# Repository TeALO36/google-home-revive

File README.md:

# Google Home Revive

Deux cartes électroniques de remplacement pour le **Google Home de 1re génération (2016)**, pour le transformer en
assistant vocal local et ouvert sous **Home Assistant** (ESPHome). Le boîtier, le haut-parleur et l'anneau lumineux
d'origine sont conservés ; l'électronique Google est remplacée.

- Carte mère : même forme et mêmes trous de fixation que l'originale, USB-C, ampli classe D, coupure micro matérielle.
- Carte du dessus : 2 micros numériques, anneau de 12 LED RGB, anneau tactile capacitif et touche centrale.
- Liaison entre les deux cartes : 10 fils soudés (des câbles Dupont coupés suffisent).
- **Les pièces délicates sont soudées en usine par JLCPCB** (micros, contrôleur tactile, ampli, USB-C, tous les petits
  passifs). Il reste à souder au fer des pièces à pattes visibles, listées plus bas avec leur emplacement.

## Aperçu des cartes

| | Face composants | Face arrière |
|---|---|---|
| Carte mère (107,6 x 49 mm, 2 couches) |  |  |
| Carte du dessus (diamètre 74,8 mm, 2 couches) |  |  |

Les deux cartes passent le contrôle DRC de KiCad sans erreur ni connexion manquante (rapports :
`hardware/*/gh_*_drc.json`).

## Fonctions

| Fonction | Réalisation |
|---|---|
| Processeur principal | ESP32-S3-WROOM-1-N16R8 (Wi-Fi, 16 Mo de flash, 8 Mo de PSRAM) |
| Mot d'activation | « Hey Jarvis » détecté sur l'appareil (micro_wake_word), pipeline vocal Home Assistant |
| Micros | 2 x Infineon IM69D130 (SNR 69 dB(A), AOP 130 dB SPL), meilleurs que les InvenSense INMP621 d'origine (65 dB(A)) |
| Annulation d'écho | référence I2S renvoyée par l'ampli (SDOUT du TAS5805M) vers l'S3 |
| Ampli | TI TAS5805M (I2S, DSP intégré, pont BTL) |
| Bluetooth | ESP32-WROOM-32E dédié en récepteur A2DP, flashé à travers l'S3 |
| Tactile | MPR121 : anneau de 10 secteurs (rotation horaire = volume +, antihoraire = volume -) et touche ronde au centre ; appui bref n'importe où = pause / lecture, double appui = piste suivante |
| LED | 12 LED RGB adressables WS2812B-MINI-V3J (couleur 24 bits réglable LED par LED) sous le diffuseur d'origine : animations arc-en-ciel, comète, scintillement, etc., pilotables depuis Home Assistant |
| Coupure micro | interrupteur matériel : l'horloge des micros est coupée physiquement, l'état est lu par l'S3 |
| Alimentation / service | USB-C vertical (flash, journaux) |
| Configuration Wi-Fi | point d'accès + page de configuration, l'adresse IP est annoncée à voix haute |

Cahier des charges complet : [docs/cahier_des_charges.md](docs/cahier_des_charges.md).

## Coût

Prix relevés le 14/11/2026 (devis JLCPCB, stock JLC et LCSC), taux 1 $ = 0,86 EUR, livraison en France, TVA 20 % et
taxe petits colis comprises. Une seule commande JLCPCB + LCSC, sous le seuil de 150 EUR (pas de frais de dédouanement).

| Commande | USD TTC | EUR TTC |
|---|---:|---:|
| **1 appareil** (+ 1 jeu de cartes pré-assemblées en réserve) | **129,13** | **111,06** |
| **2 appareils** dans la même commande | **142,27** | **122,35** |
| **Coût moyen par appareil, commande de 2** | **71,13** | **61,17** |

JLCPCB assemble au minimum **2 exemplaires** de chaque carte et fabrique au minimum **5 PCB**. Le 2e jeu assemblé coûte
environ 20 $ (20 EUR TTC) de plus que le 1er ; les 3 PCB nus restants sont compris dans le prix minimum de 5. Le plus
rentable est donc d'en faire deux (ou de partager la commande). Avec l'application de bureau JLCPCB, les PCB sont
4 $ moins chers : 106,93 EUR pour 1 appareil, 59,11 EUR par appareil pour 2.

Détail ligne par ligne : [docs/devis_partiel.md](docs/devis_partiel.md). Autres scénarios : tout assemblé par JLCPCB
(~129 EUR par appareil, [docs/devis_assemble.md](docs/devis_assemble.md)), ou kit entièrement soudé à l'air chaud
(~71 EUR, [docs/devis.md](docs/devis.md)).

## Commander

Chaque carte a trois fichiers dans `hardware/<carte>/fab/` :

| Fichier | Où l'envoyer | Contenu |
|---|---|---|
| `gh_<carte>_gerbers.zip` | JLCPCB | le circuit imprimé |
| `gh_<carte>_bom.csv` + `gh_<carte>_cpl.csv` | JLCPCB (assemblage) | pièces soudées en usine et leur position |
| `gh_<carte>_hand_bom.csv` | LCSC (pas JLCPCB) | pièces à souder soi-même |

### 1. JLCPCB : PCB + assemblage des pièces délicates

À faire deux fois, d'abord pour `mainboard`, puis pour `topboard` :

1. Sur jlcpcb.com, « Order now », puis « Add gerber file » : choisir `gh_<carte>_gerbers.zip`.
2. Options du PCB : 2 couches, épaisseur 1,6 mm, finition **HASL sans plomb** (« LeadFree HASL », exigée pour
   l'assemblage), vias « Tented », quantité 5.
3. En bas de la page, activer **« PCB Assembly »** :
   - type **Economic** ;
   - face assemblée **Top** ;
   - quantité assemblée **2** (minimum imposé) ;
   - valider.
4. Page suivante : « Add BOM File » = `gh_<carte>_bom.csv`, « Add CPL File » = `gh_<carte>_cpl.csv`, puis
   « Process BOM & CPL ».
5. Liste des pièces : toutes doivent être trouvées et cochées. Si une pièce est en rupture, choisir un équivalent de
   même valeur et même boîtier. Ne pas téléverser `gh_<carte>_hand_bom.csv` ici.
6. Vérification des placements : la vue montre chaque pièce sur la carte. Contrôler l'orientation du TAS5805M (U3),
   du transistor Q1 et de l'USB-C (J1) pour la carte mère, des micros (MK1, MK2) et du MPR121 (U1) pour la carte du
   dessus : les pattes doivent tomber sur les pastilles et le point rose (broche 1) sur le repère triangulaire de la
   sérigraphie. Une pièce tournée ou décalée se corrige dans cette vue : la sélectionner, puis boutons de rotation ou
   flèches du clavier. Les ingénieurs JLCPCB revérifient aussi les placements avant la production.
   Seules les pièces de `gh_<carte>_bom.csv` apparaissent : les modules ESP32, bobines, C1, etc. sont absents, c'est
   normal (à souder soi-même).
7. « Save to cart ».

Les deux cartes se paient ensemble dans le panier. Appliquer le coupon SMT mensuel (9 $) s'il est proposé.

### 2. LCSC : pièces à souder soi-même

1. Sur lcsc.com, ouvrir l'outil « BOM Tool » et téléverser `hardware/mainboard/fab/gh_mainboard_hand_bom.csv`, puis
   `hardware/topboard/fab/gh_topboard_hand_bom.csv` (colonne « LCSC Part # »).
2. Pour 2 appareils, doubler les quantités. LCSC impose parfois un minimum (5 ou 10 pièces pour les petits circuits) :
   accepter, le surplus coûte quelques centimes.
3. Au paiement, regrouper l'envoi avec la commande JLCPCB (option de colis combiné) pour payer une seule livraison.
4. Ajouter un paquet de **câbles Dupont femelle-femelle de 20 cm** (n'importe quel vendeur) si vous n'en avez pas.

Avant de commander, vérifier la mécanique (section 8 du cahier des charges) sur l'appareil réel.

## Ce qu'il faut souder soi-même

<p align="center">
  
</p>

Le [manuel de soudure](docs/manuel_soudure.md) reprend tout pas à pas : liste des composants face par face, plans,
technique pour chaque type de pièce, fils de liaison et contrôles avant la mise sous tension. Résumé ci-dessous.

Les cartes arrivent avec les pièces délicates déjà soudées. Restent uniquement des pièces dont les pattes sont visibles
et accessibles à la panne du fer. Sur les plans, **en orange : à souder soi-même**, en gris : déjà soudé par JLCPCB.

Outillage : fer à panne fine (biseau 1 à 2 mm), étain 0,5 mm, flux, tresse à dessouder, pince brucelles, loupe.
Pas d'air chaud nécessaire. Ordre conseillé : petits circuits d'abord, puis bobines, condensateur, modules, connecteur.

### Carte mère (face composants)

| Repère | Pièce | Lien LCSC | Qté | Boîtier | Variantes et pièges |
|---|---|---|---:|---|---|
| U1 | ESP32-S3-WROOM-1-N16R8 | [C2913202](https://www.lcsc.com/product-detail/C2913202.html) | 1 | module 18 x 25,5 mm, pattes crénelées | N8R8 ou N16R2 conviennent (PSRAM obligatoire). Éviter WROOM-1U (antenne externe), WROOM-2 et MINI (brochage différent). |
| U2 | ESP32-WROOM-32E-N4 | [C701341](https://www.lcsc.com/product-detail/C701341.html) | 1 | module 18 x 25,5 mm | N8 / N16 conviennent. Éviter WROOM-32UE (antenne externe) et WROVER. |
| U4 | TPS54302DDCR | [C311983](https://www.lcsc.com/product-detail/C311983.html) | 1 | SOT-23-6 (« DDC ») | Régulateur 5 V. Pas de TPS54202 (autre brochage). |
| U5 | TLV62569DBVR | [C141836](https://www.lcsc.com/product-detail/C141836.html) | 1 | SOT-23-5 (« DBV ») | Régulateur 3,3 V. Pas la version DRL (boîtier SOT-563, plus petit). |
| U6 | USBLC6-2SC6 | [C7519](https://www.lcsc.com/product-detail/C7519.html) | 1 | SOT-23-6 | Protection USB. Repère du point = broche 1. |
| U7 | 74LVC1G74DP | [C548409](https://www.lcsc.com/product-detail/C548409.html) | 1 | TSSOP-8 3 x 3 mm (« DP ») | Bascule du mute. Pas les suffixes DC ou GT (boîtiers plus petits). |
| U8 | SN74LVC1G14DBVR | [C7835](https://www.lcsc.com/product-detail/C7835.html) | 1 | SOT-23-5 (« DBV ») | Pas la version DCK (SC-70, plus petite). |
| U9 | SN74LVC1G125DBVR | [C23654](https://www.lcsc.com/product-detail/C23654.html) | 1 | SOT-23-5 (« DBV ») | Pas la version DCK. |
| L1 | 10 uH | [C602032](https://www.lcsc.com/product-detail/C602032.html) | 1 | bobine blindée 4 x 4 mm | Toute bobine blindée 4 x 4 mm de même valeur et de courant au moins égal. |
| L2 | 2,2 uH | [C602029](https://www.lcsc.com/product-detail/C602029.html) | 1 | bobine blindée 4 x 4 mm | idem |
| L3, L4 | 4,7 uH | [C602031](https://www.lcsc.com/product-detail/C602031.html) | 2 | bobine blindée 4 x 4 mm | idem (filtre de sortie de l'ampli) |
| C1 | 220 uF / 25 V | [C696188](https://www.lcsc.com/product-detail/C696188.html) | 1 | électrolytique CMS 6,3 x 6,6 mm | **Polarisé** : la bande noire (moins) va du côté du coin non biseauté de l'empreinte. 25 V minimum. |
| J3 | JST ZH 2 broches, CMS horizontal | [C265329](https://www.lcsc.com/product-detail/C265329.html) | 1 | S2B-ZR-SM4A-TF | Connecteur du haut-parleur. Réutiliser la fiche d'origine si elle est au pas de 1,5 mm, sinon souder les fils sur les pastilles. |

### Carte mère (face arrière)

Une seule pièce : le **jack d'alimentation d'origine** (J2), à dessouder de la carte Google et à ressouder au même
endroit (empreinte copiée de l'originale, 2 ergots de centrage). Il n'est pas commandé : on réutilise le sien.

Les deux modules ESP32 se soudent comme de gros composants : étamer une pastille d'angle, poser le module, chauffer
l'angle, vérifier l'alignement, puis souder les autres pattes. Le plan de masse sous le module n'a pas besoin d'être
soudé.

### Carte du dessus

Face arrière (vue carte retournée) : les 12 LED, tournées vers le diffuseur.

Face composants : le tampon de niveau des LED.

| Repère | Pièce | Lien LCSC | Qté | Boîtier | Variantes et pièges |
|---|---|---|---:|---|---|
| D1 à D12 | WS2812B-MINI-V3J | [C22371519](https://www.lcsc.com/product-detail/C22371519.html) | 12 | 3,5 x 3,5 mm, 4 pattes en J | Uniquement cette version « MINI-V3J » : les WS2812B-2020 ou 1515 n'ont pas de pattes accessibles au fer, la WS2812B 5050 est trop grande. Orientation : broche 1 = VDD (+5 V), suivre le plan KiCad (`hardware/topboard/gh_topboard.kicad_pcb`). |
| U2 | SN74AHCT1G125DBVR | [C7484](https://www.lcsc.com/product-detail/C7484.html) | 1 | SOT-23-5 (« DBV ») | **AHCT** obligatoire (entrée compatible 3,3 V, sortie 5 V) : pas de version AHC ni LVC. |

Les photos et la documentation de chaque pièce sont sur sa page LCSC (lien ci-dessus) : comparer le boîtier et le
marquage avant de commander une variante.

### Liaison entre les cartes : 10 fils

Pastilles J4 (carte mère) et J1 (carte du dessus), au pas de 2,54 mm, dans cet ordre :

| Broche | Signal | Broche | Signal |
|---|---|---|---|
| 1 | +5 V | 6 | SCL |
| 2 | GND | 7 | VMIC |
| 3 | données LED | 8 | DAT (micros) |
| 4 | +3,3 V | 9 | GND |
| 5 | SDA | 10 | CLK (micros) |

1. Prendre une nappe de 10 câbles Dupont femelle-femelle de 20 cm (ils restent collés côte à côte).
2. Couper les connecteurs aux deux bouts, garder une longueur de **12 à 15 cm**.
3. Dénuder 2 mm, torsader les brins, étamer.
4. Étamer les pastilles, poser chaque fil à plat sur sa pastille et chauffer. Même ordre des deux côtés.
5. **Torsader ensemble les fils 9 (GND) et 10 (CLK)** sur toute la longueur.
6. Vérifier au multimètre qu'il n'y a pas de court-circuit entre +5 V, +3,3 V et GND avant la première mise sous tension.

Variante démontable : souder une barrette de 10 broches mâles CMS au pas de 2,54 mm sur J4 de la carte mère et
garder les connecteurs Dupont de ce côté.

## Firmware

### Premier flash (ESP32-S3, ESPHome)

```bash
pip install esphome
cd firmware/s3
cp secrets.example.yaml secrets.yaml      # Wi-Fi (facultatif), mots de passe et clé API
esphome run gh-revive.yaml                # brancher l'USB-C ; ensuite les mises à jour passent par OTA
```

Si l'S3 n'est pas détecté, maintenir la pastille TP2 (BOOT) à la masse en branchant l'USB-C.

### Configuration du Wi-Fi

- **Identifiants au flash** : renseigner `wifi_ssid` / `wifi_password` dans `secrets.yaml`, l'appareil s'y connecte
  directement.
- **Sans identifiants** (ou réseau injoignable pendant 30 s) : l'appareil ouvre le point d'accès **« GH-Revive
  Setup »** (mot de passe : `ap_password` de `secrets.yaml`) et le haut-parleur le dit toutes les minutes. En s'y
  connectant, le téléphone ouvre la page de configuration :
  1. **mot de passe administrateur** : créé à la première visite (8 caractères minimum, saisi deux fois), demandé
     ensuite pour toute modification ;
  2. **réseau Wi-Fi** : choisi dans la liste des réseaux détectés ou saisi à la main, puis la clé ;
  3. la connexion est **testée en direct** : « clé incorrecte », « réseau introuvable » ou « sécurité non prise en
     charge » s'affichent, et l'on corrige pour réessayer.
- Une fois connecté, le haut-parleur **annonce l'adresse IP** (« Connecté au Wi-Fi. Mon adresse est : 1 9 2 point
  1 6 8 ... »). Le bouton « Annoncer l'adresse IP » dans Home Assistant la répète.
- La même page reste accessible sur le réseau local à `http://<adresse IP>/`, protégée par le mot de passe
  administrateur.
- **WEP** : non pris en charge. La pile Wi-Fi de l'ESP32 ne gère que WPA, WPA2 et WPA3 ; le WEP est cassable en
  quelques minutes et absent des box récentes. Passer la box en WPA2.

### Plusieurs appareils dans la maison

Aucune intégration Home Assistant spécifique n'est nécessaire : chaque appareil est un appareil ESPHome standard,
découvert automatiquement par l'intégration ESPHome de Home Assistant.

- **Même firmware pour tous** : le nom reçoit automatiquement la fin de l'adresse MAC (`gh-revive-a1b2c3`), donc
  plusieurs appareils cohabitent sans conflit. On les renomme ensuite dans Home Assistant (« Salon », « Chambre »).
- **Une pièce par appareil** : assigner chaque appareil à sa pièce (« Zone » dans Home Assistant). « Jarvis, allume la
  lumière » allume alors la lumière de la pièce où se trouve l'appareil qui a répondu.
- **Où se règle le mot d'activation** : réglage « Detection du mot d'activation » de chaque enceinte.
  - « Sur l'appareil » (par défaut) : l'enceinte reconnaît elle-même « Hey Jarvis », « Okay Nabu » ou « Hey Mycroft » ;
    le mot se choisit dans Home Assistant, page de l'appareil (« Mot d'activation »). Le micro ne part vers le serveur
    qu'après le mot d'activation, et l'arbitrage de proximité ci-dessous fonctionne.
  - « Dans Home Assistant » : c'est le moteur de mot d'activation du pipeline Assist qui décide (module openWakeWord à
    installer, puis Paramètres > Assistants vocaux > Assist > mot d'activation). Le mot réglé dans Assist vaut pour
    toutes les enceintes réglées ainsi, y compris un modèle personnalisé. En contrepartie, chaque enceinte envoie le
    son du micro au serveur en continu, et l'arbitrage de proximité ne s'applique pas (Home Assistant garde la
    première enceinte qui l'a entendu).
  - Le téléphone se règle à part, dans l'application.
- **L'enceinte la plus proche répond** : quand plusieurs enceintes entendent le mot d'activation, chacune envoie aux
  autres (UDP, port 18511, réseau local) le volume auquel elle l'a entendu, attend le « Delai d'arbitrage » (400 ms
  par défaut), et seule la plus forte démarre l'écoute. Dans une pièce ouverte avec mezzanine, l'enceinte de la
  chambre répond quand on parle depuis le lit. « Niveau dernier mot d'activation » (diagnostic) montre le volume
  mesuré ; « Correction niveau micro » (±15 dB) compense une enceinte posée dans un coin ou derrière un objet.
- **Le téléphone en main est prioritaire** : le téléphone ne participe pas à l'arbitrage, mais il envoie le son à Home
  Assistant dès qu'il entend le mot d'activation, pendant que les enceintes attendent encore. Home Assistant garde le
  premier arrivé : si le téléphone a entendu, c'est lui qui répond et affiche le texte compris. Si le téléphone gagne
  trop rarement, augmenter le « Delai d'arbitrage » (jusqu'à 1,5 s, réponse un peu plus lente).
- **Pas de double exécution** : Home Assistant refuse tout second démarrage pour le même mot d'activation
  (`duplicate_wake_up_detected`), ce qui couvre aussi une annonce UDP perdue. Une commande n'est exécutée qu'une fois.
  Sur les appareils écartés, l'anneau reste éteint, sans signal d'erreur.
- **Texte compris et réponse** : « Derniere demande » et « Derniere reponse » affichent dans l'application Home
  Assistant ce que l'enceinte a compris et répondu (page de l'appareil ou carte de tableau de bord).
- **Sensibilité** : « Sensibilite mot d'activation » (Faible / Normale / Forte) règle chaque appareil, pour tous les
  modèles.
- Configurer les appareils un par un : tant qu'ils ne sont pas connectés, ils ouvrent tous le même point d'accès
  « GH-Revive Setup ».

### Module Bluetooth (PlatformIO)

Le module Bluetooth n'a pas de port USB : l'S3 sert de pont USB-C vers le module le temps de le programmer.

```bash
cd firmware/bt
pio run -e bridge -t upload --upload-port COMx    # l'S3 devient un pont USB <-> UART vers le module
pio run -e bt -t upload --upload-port COMy        # programme le module (nouveau port COM du pont)
esphome run ../s3/gh-revive.yaml                  # remet le firmware principal sur l'S3
```

### Tests unitaires (sur PC)

```bash
g++ -std=c++17 -Wall -Wextra -Werror -I firmware/s3 firmware/tests/test_ring_gesture.cpp -o test_ring && ./test_ring
g++ -std=c++17 -Wall -Wextra -Werror -I firmware/s3 firmware/tests/test_ip_speech.cpp -o test_ip && ./test_ip
g++ -std=c++17 -Wall -Wextra -Werror -I firmware/s3 firmware/tests/test_wake_arbiter.cpp -o test_arbiter && ./test_arbiter
```

### État du firmware

Fonctionnel dans la configuration : Wi-Fi avec portail de configuration et annonce vocale de l'IP, OTA, mot
d'activation et assistant vocal, lecteur multimédia avec atténuation pendant la voix, démarrage de l'ampli, anneau
tactile, LED, mute, pilotage du module Bluetooth. Reste à développer : l'annulation d'écho avec ESP-SR (composant ESP-IDF
dédié) et le relais du flux Bluetooth vers l'ampli (l'S3 n'a que deux périphériques I2S, voir la section 10 du cahier
des charges).

Messages vocaux : voix Piper `fr_FR-siwis-medium` (corpus SIWIS, licence CC BY 4.0), voir
[firmware/s3/sounds/README.md](firmware/s3/sounds/README.md).

## Contenu du dépôt

```
hardware/
  mainboard/            carte mère : projet KiCad 10, aperçus, rapport DRC
    fab/                gerbers.zip, bom.csv + cpl.csv (JLCPCB), hand_bom.csv (LCSC)
  topboard/             carte du dessus : idem
  lib/gh_revive.pretty  empreintes spécifiques (micros, LED, électrodes, pastilles de liaison)
firmware/
  s3/                   ESPHome pour l'ESP32-S3 (voix, média, tactile, LED, ampli, mute, Wi-Fi)
    components/gh_setup portail de configuration Wi-Fi (mot de passe admin, test de clé)
    sounds/             messages vocaux FLAC et leur générateur
  bt/                   PlatformIO : récepteur Bluetooth A2DP + pont de flashage USB
  homeassistant/        automatisation des gestes (double tap = piste suivante)
  tests/                tests unitaires (gestes, annonce de l'IP)
docs/                   cahier des charges, devis, plans de soudure (img/)
tools/                  génération des cartes (KiCad Python + FreeRouting) et calcul des devis
```

## Régénérer les cartes

Les cartes sont décrites en Python (`tools/ghrevive/`) et générées avec KiCad 10 et FreeRouting :

```bash
"C:/Program Files/KiCad/10.0/bin/python.exe" tools/build.py all              # placement, routage, DRC, fichiers JLC, plans
"C:/Program Files/KiCad/10.0/bin/python.exe" tools/quote_partial.py          # devis retenu
"C:/Program Files/KiCad/10.0/bin/python.exe" tools/quote_assembled.py        # devis tout assemblé
"C:/Program Files/KiCad/10.0/bin/python.exe" tools/quote.py                  # devis kit
```

La répartition usine / soudure manuelle se règle dans `HAND_REFS` (`tools/ghrevive/mainboard.py`) et le champ
`hand=True` des pièces (`tools/ghrevive/topboard.py`).

## Licence

MIT, voir [LICENSE](LICENSE). Projet indépendant, sans lien avec Google. « Google Home » est une marque de Google LLC.
Messages vocaux sous CC BY 4.0 (voir ci-dessus).

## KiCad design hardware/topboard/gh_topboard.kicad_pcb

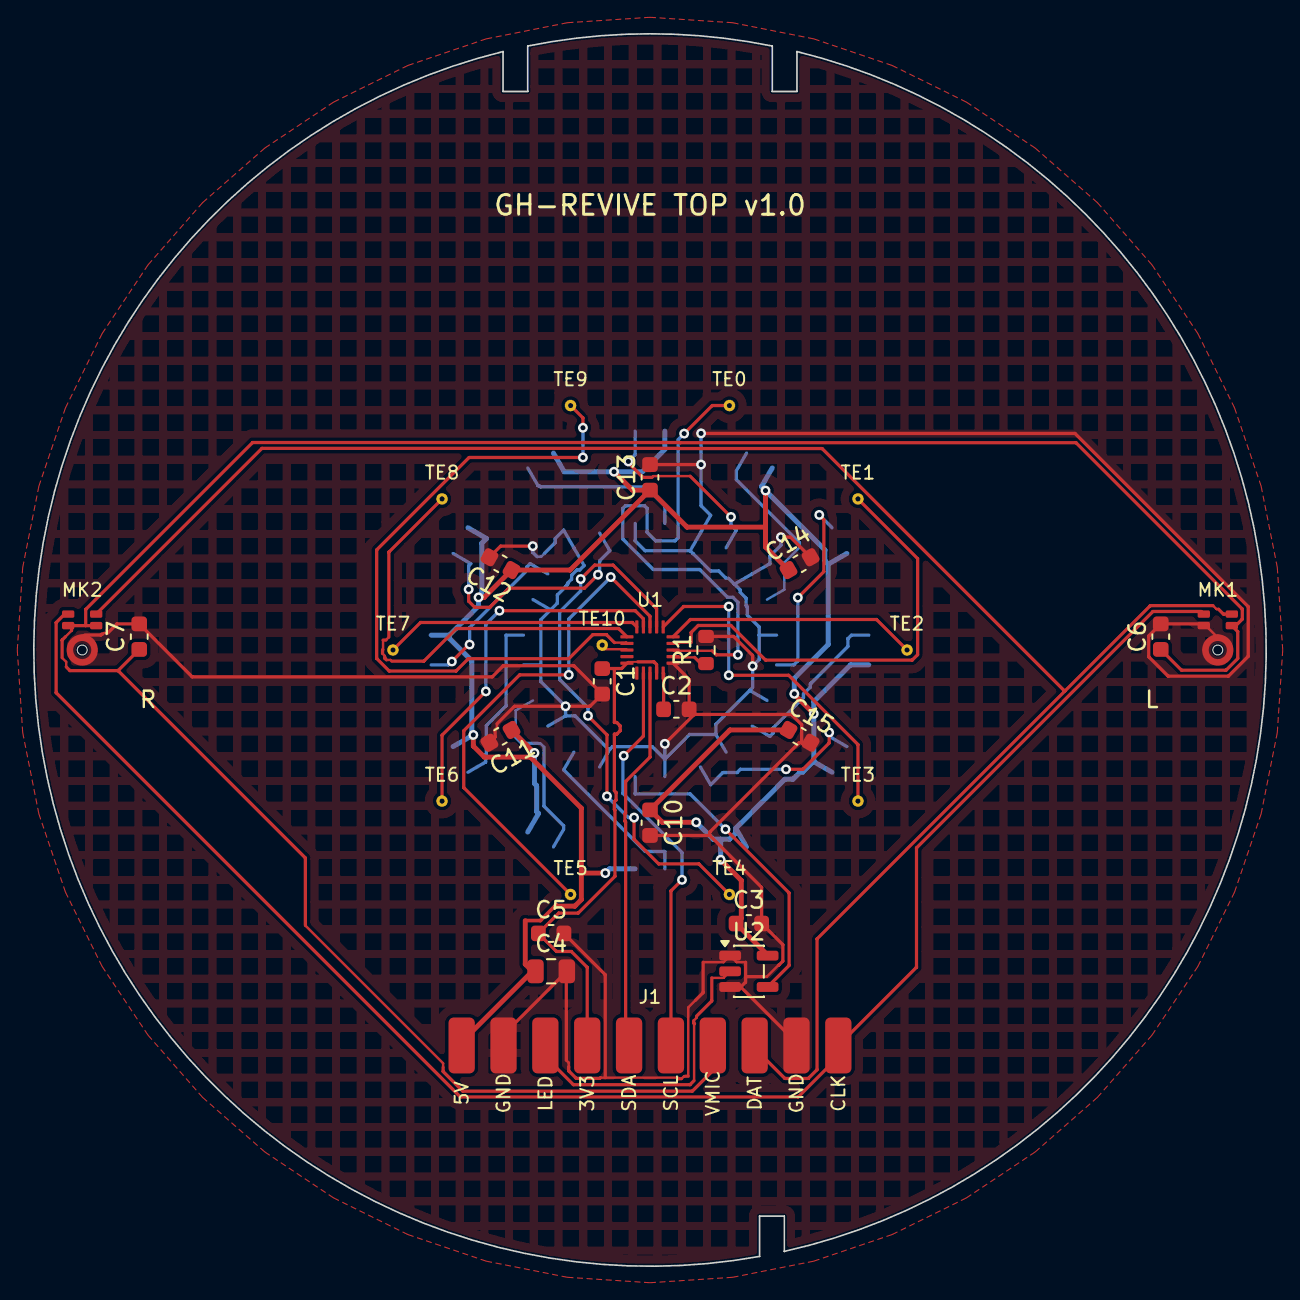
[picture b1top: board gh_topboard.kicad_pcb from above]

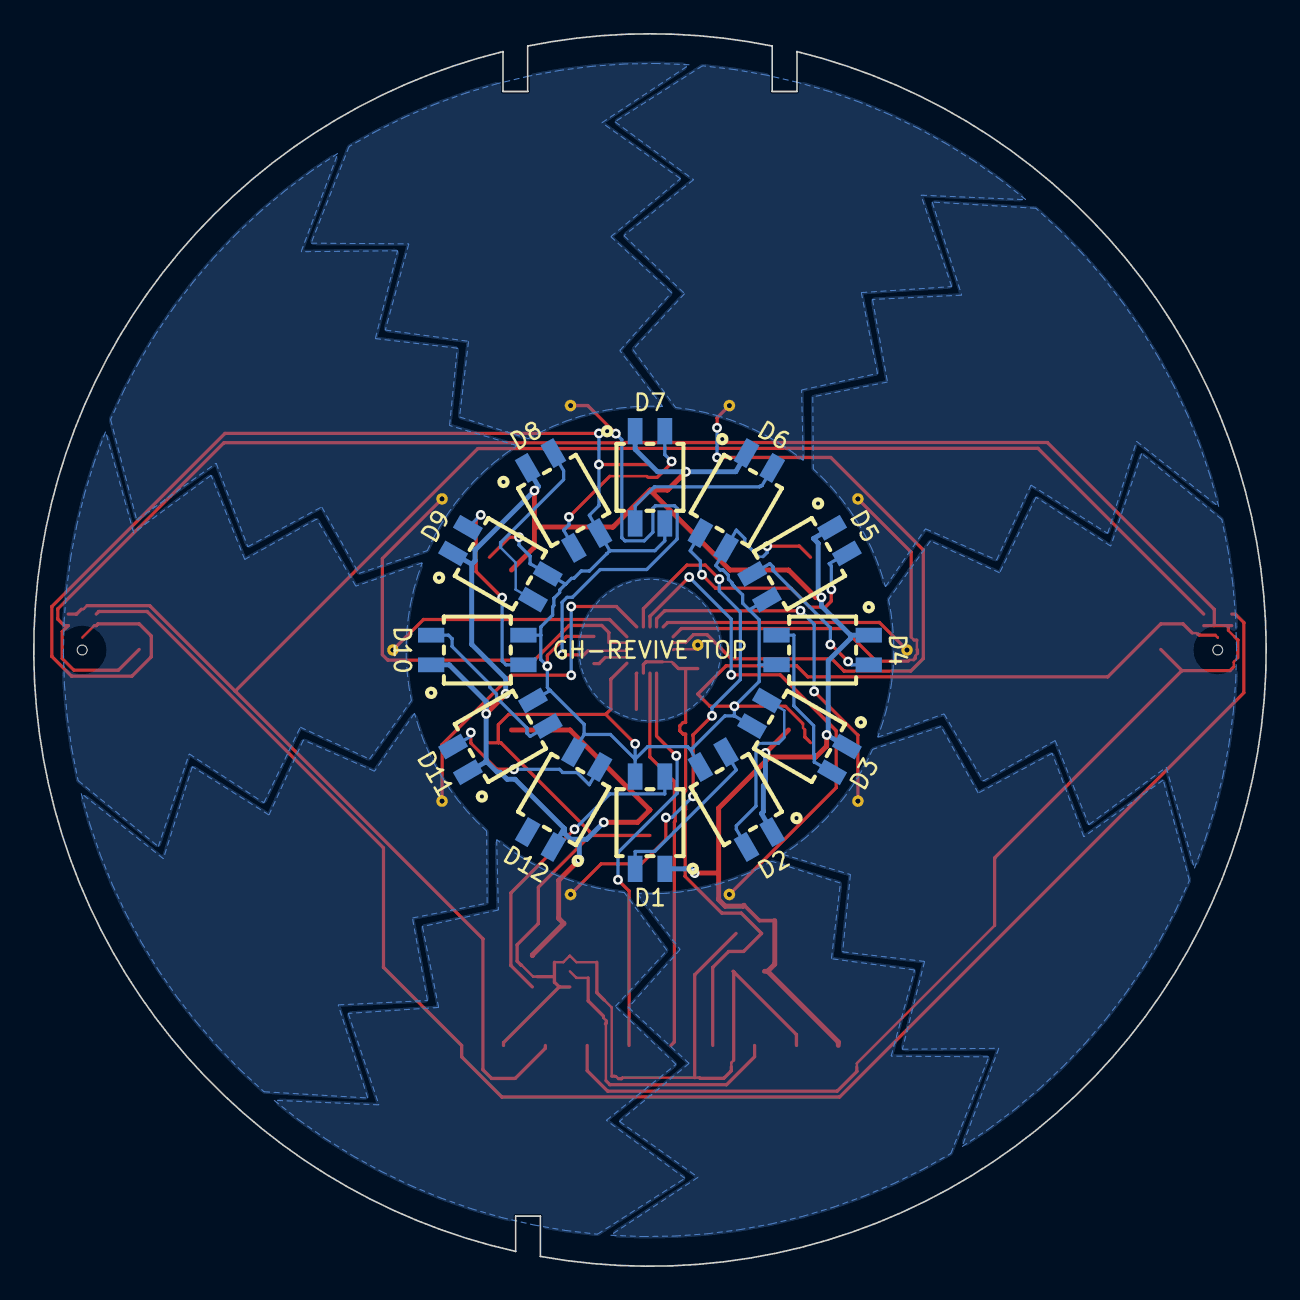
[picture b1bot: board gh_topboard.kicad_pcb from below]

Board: 2 copper layers, 74.8 x 74.8 mm, 42 parts (12 on the bottom side), 34 nets.

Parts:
C1, C2, C3, C6, C7, C10, C11, C12, C13, C14, C15: 100nF; C_0603_1608Metric
C4: 22uF/25V; C_0805_2012Metric
C5: 1uF; C_0603_1608Metric
D1, D2, D3, D4, D5, D6, D7, D8, D9, D10, D11, D12: WS2812B-MINI-V3J; LED-SMD_4P-L3.5-W3.5-P1.80-LS6.2_WS2812B-MINI-V3J
J1: MAIN_LINK; GH_WirePads_1x10_P2.54mm
MK1, MK2: IM69D130; GH_MIC_IM69D130
R1: 75k; R_0603_1608Metric
TE0: TAP_0; GH_ElectrodeTap
TE1: TAP_1; GH_ElectrodeTap
TE2: TAP_2; GH_ElectrodeTap
TE3: TAP_3; GH_ElectrodeTap
TE4: TAP_4; GH_ElectrodeTap
TE5: TAP_5; GH_ElectrodeTap
TE6: TAP_6; GH_ElectrodeTap
TE7: TAP_7; GH_ElectrodeTap
TE8: TAP_8; GH_ElectrodeTap
TE9: TAP_9; GH_ElectrodeTap
TE10: TAP_CENTRE; GH_ElectrodeTap
U1: MPR121QR2; GH_QFN20_MPR121
U2: SN74AHCT1G125DBVR; SOT-23-5

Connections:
+3V3: C1.1, C5.1, J1.4, U1.4, U1.20
+5V: C3.1, C4.1, C10.1, C11.1, C12.1, C13.1, C14.1, C15.1, D1.1, D2.1, D3.1, D4.1, D5.1, D6.1, D7.1, D8.1, D9.1, D10.1, D11.1, D12.1, J1.1, U2.5
ELE0: TE0.1, U1.8
ELE1: TE1.1, U1.9
ELE2: TE2.1, U1.10
ELE3: TE3.1, U1.11
ELE4: TE4.1, U1.12
ELE5: TE5.1, U1.13
ELE6: TE6.1, U1.14
ELE7: TE7.1, U1.15
ELE8: TE8.1, U1.16
ELE9: TE9.1, U1.17
ELE10: TE10.1, U1.18
GND: C1.2, C2.2, C3.2, C4.2, C5.2, C6.2, C7.2, C10.2, C11.2, C12.2, C13.2, C14.2, C15.2, D1.3, D2.3, D3.3, D4.3, D5.3, D6.3, D7.3, D8.3, D9.3, D10.3, D11.3, D12.3, J1.2, J1.9, MK1.4, MK1.5, MK2.5, R1.2, U1.6, U2.1, U2.3
I2C_SCL: J1.6, U1.2
I2C_SDA: J1.5, U1.3
LED_D0: D1.4, U2.4
LED_D1: D1.2, D2.4
LED_D2: D2.2, D3.4
LED_D3: D3.2, D4.4
LED_D4: D4.2, D5.4
LED_D5: D5.2, D6.4
LED_D6: D6.2, D7.4
LED_D7: D7.2, D8.4
LED_D8: D8.2, D9.4
LED_D9: D9.2, D10.4
LED_D10: D10.2, D11.4
LED_D11: D11.2, D12.4
LED_DATA: J1.3, U2.2
MPR_REXT: R1.1, U1.7
MPR_VREG: C2.1, U1.5
PDM_CLK: J1.10, MK1.3, MK2.3
PDM_DAT: J1.8, MK1.1, MK2.1
VMIC: C6.1, C7.1, J1.7, MK1.2, MK2.2, MK2.4

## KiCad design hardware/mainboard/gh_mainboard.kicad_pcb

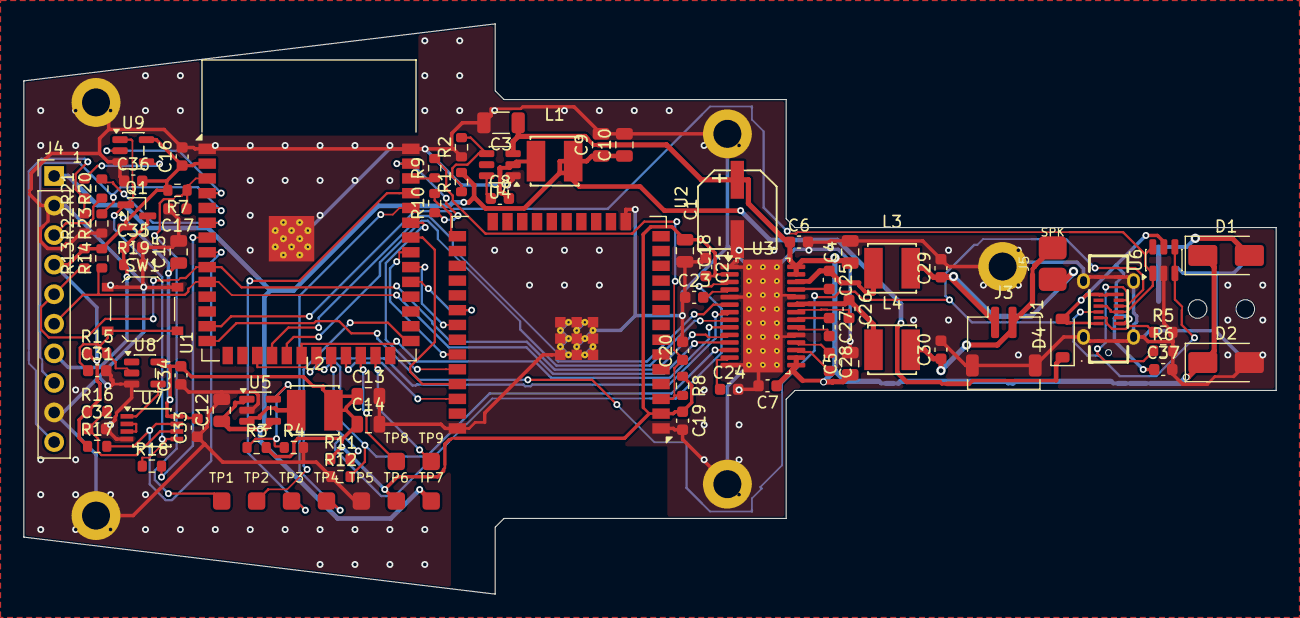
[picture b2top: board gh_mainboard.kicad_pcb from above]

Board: 2 copper layers, 107.6 x 49.0 mm, 94 parts (1 on the bottom side), 65 nets.

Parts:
C1: 220uF/25V; CAP-SMD_BD6.3-L6.6-W6.6-RD
C3: 10uF/50V; C_1206_3216Metric
C4, C5, C9, C10, C12, C13, C14, C15, C18: 22uF/25V; C_0805_2012Metric
C6, C7, C8, C16, C19, C21, C31, C32, C33, C34, C36: 100nF; C_0603_1608Metric
C17, C20, C23, C24, C29, C30, C35, C37: 1uF; C_0603_1608Metric
C25, C26, C27, C28: 470nF; C_0603_1608Metric
D1: SS54; D_SMA
D2: SMAJ18A; D_SMA
D4: B5819W; D_SOD-123
H1, H2, H3, H4, H5: Hole_2.4mm; MountingHole
J1: USB-C; USB-C-SMD_TYPEC-303-ACP16
J2: DC_JACK_ORIGINAL; GH_DCJack_Original
J3: SPEAKER; JST_ZH_S2B-ZR-SM4A-TF_1x02-1MP_P1.50mm_Horizontal
J4: TOP_LINK; PinHeader_1x10_P2.54mm_Vertical
J5: SPK_PADS; GH_SpeakerPads
L1: 10uH; IND-SMD_L4.0-W4.0
L2: 2.2uH; IND-SMD_L4.0-W4.0
L3, L4: 4.7uH; IND-SMD_L4.0-W4.0
Q1: AO3401A; SOT-23
R1: 75k; R_0603_1608Metric
R2, R7, R8, R12, R17, R19, R22: 10k; R_0603_1608Metric
R3, R15, R16, R18, R23: 100k; R_0603_1608Metric
R4: 22k; R_0603_1608Metric
R5, R6: 5.1k; R_0603_1608Metric
R9, R10: 1k; R_0603_1608Metric
R11, R13, R14: 4.7k; R_0603_1608Metric
R20, R21: 33R; R_0603_1608Metric
SW1: MUTE; SW_Push_1P1T_XKB_TS-1187A
TP1: EN; GH_TestPad_1.5mm
TP2: BOOT; GH_TestPad_1.5mm
TP3: TX; GH_TestPad_1.5mm
TP4: RX; GH_TestPad_1.5mm
TP5: GND; GH_TestPad_1.5mm
TP6: 3V3; GH_TestPad_1.5mm
TP7: 5V; GH_TestPad_1.5mm
TP8: IO47; GH_TestPad_1.5mm
TP9: IO48; GH_TestPad_1.5mm
U1: ESP32-S3-WROOM-1-N16R8; ESP32-S3-WROOM-1
U2: ESP32-WROOM-32E-N4; ESP32-WROOM-32E
U3: TAS5805MPWPR; TSSOP-28-1EP_4.4x9.7mm_P0.65mm_EP3.4x9.7mm_Mask3.1x4.05mm_T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
U4: TPS54302DDCR; SOT-23-6
U5: TLV62569DBVR; SOT-23-5
U6: USBLC6-2SC6; SOT-23-6
U7: 74LVC1G74DP; TSSOP-8_3x3mm_P0.65mm
U8: SN74LVC1G14DBVR; SOT-23-5
U9: SN74LVC1G125DBVR; SOT-23-5

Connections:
+3V3: C13.1, C14.1, C15.1, C16.1, C18.1, C19.1, C21.2, C33.2, C34.2, C36.2, J4.4, L2.2, Q1.2, R3.2, R7.2, R8.1, R11.1, R13.2, R14.2, R15.1, R16.1, R17.1, TP6.1, U1.2, U2.2, U3.2, U7.8, U8.5, U9.5
+5V: C9.1, C10.1, C12.1, D4.1, J4.1, L1.2, R1.2, TP7.1, U5.1, U5.4
AMP_AVDD: C24.1, U3.13
AMP_FAULT: R11.2, U1.22, U3.3
AMP_PDN: R12.2, U1.21, U3.12
AMP_VR_DIG: C23.2, U3.4
BOOT_5V: C8.1, U4.6
BST_A_N: C26.2, U3.22
BST_A_P: C25.2, U3.25
BST_B_N: C27.1, U3.21
BST_B_P: C28.1, U3.18
BT_BCLK: U1.31, U2.30
BT_BOOT: R10.2, U2.25
BT_BOOT_CTL: R10.1, U1.39
BT_DATA: U1.33, U2.33
BT_EN: C20.1, R8.2, R9.2, U2.3
BT_EN_CTL: R9.1, U1.38
BT_GPIO: U1.23, U2.36
BT_LRCK: U1.32, U2.31
BT_RXD: U1.35, U2.34
BT_TXD: U1.34, U2.35
FB_3V3: R3.1, R4.1, U5.5
FB_5V: R1.1, R2.2, U4.4
GND: C1.2, C3.2, C4.2, C5.2, C6.2, C7.2, C9.2, C10.2, C12.2, C13.2, C14.2, C15.2, C16.2, C17.2, C18.2, C19.2, C20.2, C21.1, C23.1, C24.2, C29.2, C30.2, C31.2, C32.2, C33.1, C34.1, C35.2, C36.1, C37.2, D2.2, H1.1, H2.1, H3.1, H4.1, H5.1, J1.1, J1.2, J1.3, J1.4, J1.A1, J1.A12, J1.B1, J1.B12, J2.MP1, J2.MP2, J2.SLV, J2.SW, J3.MP, J4.2, J4.9, R2.1, R4.2, R5.2, R6.2, R12.1, R19.2, R22.1, R23.1, SW1.1, TP5.1, U1.1, U1.40, U1.41, U2.1, U2.15, U2.38, U2.39, U3.1, U3.5, U3.14, U3.19, U3.24, U3.29, U4.1, U5.2, U6.2, U7.4, U8.3, U9.3
I2C_SCL: J4.6, R14.1, U1.10, U3.11
I2C_SDA: J4.5, R13.1, U1.9, U3.10
I2S_BCLK: U1.17, U3.7
I2S_DOUT: U1.19, U3.8
I2S_LRCK: U1.18, U3.6
I2S_REF: U1.20, U3.9
LED_DATA: J4.3, R20.1
LED_DATA_S3: R20.2, U1.6
MIC_OFF: Q1.1, R18.1, U7.5, U9.1
MUTE_BTN: C31.1, R15.2, SW1.2, U8.2
MUTE_CLK: U7.1, U8.4
MUTE_NQ: U7.2, U7.3
MUTE_POR: C32.1, R16.2, U7.6
MUTE_SET_N: R17.2, U1.8, U7.7
MUTE_STATE: R18.2, U1.7
OUT_A_N: C26.1, L4.1, U3.23
OUT_A_P: C25.1, L3.1, U3.26
OUT_B_N: C27.2, U3.20
OUT_B_P: C28.2, U3.17
PDM_CLK: J4.10, R21.1, R22.2
PDM_CLK_G: R21.2, U9.4
PDM_CLK_S3: U1.4, U9.2
PDM_DAT: J4.8, R23.2, U1.5
PVDD: C1.1, C3.1, C4.1, C5.1, C6.1, C7.1, D1.1, D2.1, U3.15, U3.16, U3.27, U3.28, U4.3
S3_BOOT: TP2.1, U1.27
S3_EN: C17.1, R7.1, TP1.1, U1.3
S3_RXD0: TP4.1, U1.36
S3_TXD0: TP3.1, U1.37
SPARE_IO47: TP8.1, U1.24
SPARE_IO48: TP9.1, U1.25
SPK_N: C30.1, J3.2, J5.2, L4.2
SPK_P: C29.1, J3.1, J5.1, L3.2
SW_3V3: L2.1, U5.3
SW_5V: C8.2, L1.1, U4.2
USB_CC1: J1.A5, R5.1
USB_CC2: J1.B5, R6.1
USB_DN: J1.A7, J1.B7, U1.13, U6.1, U6.6
USB_DP: J1.A6, J1.B6, U1.14, U6.3, U6.4
VBUS: C37.1, D4.2, J1.A4, J1.A9, J1.B4, J1.B9, U6.5
VIN_RAW: D1.2, J2.TIP
VMIC: C35.1, J4.7, Q1.3, R19.1

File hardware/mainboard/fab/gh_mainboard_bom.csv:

Comment,Designator,Footprint,LCSC Part #
22uF/25V,"C10,C12,C13,C14,C15,C18,C4,C5,C9",C_0805_2012Metric,C45783
100nF,"C16,C19,C21,C31,C32,C33,C34,C36,C6,C7,C8",C_0603_1608Metric,C14663
1uF,"C17,C20,C23,C24,C29,C30,C35,C37",C_0603_1608Metric,C15849
470nF,"C25,C26,C27,C28",C_0603_1608Metric,C1623
10uF/50V,C3,C_1206_3216Metric,C13585
SS54,D1,D_SMA,C22452
SMAJ18A,D2,D_SMA,C19077538
B5819W,D4,D_SOD-123,C8598
USB-C,J1,USB-C-SMD_TYPEC-303-ACP16,C720628
AO3401A,Q1,SOT-23,C15127
75k,R1,R_0603_1608Metric,C23242
1k,"R10,R9",R_0603_1608Metric,C21190
4.7k,"R11,R13,R14",R_0603_1608Metric,C23162
10k,"R12,R17,R19,R2,R22,R7,R8",R_0603_1608Metric,C25804
100k,"R15,R16,R18,R23,R3",R_0603_1608Metric,C25803
33R,"R20,R21",R_0603_1608Metric,C23140
22k,R4,R_0603_1608Metric,C31850
5.1k,"R5,R6",R_0603_1608Metric,C23186
MUTE,SW1,SW_Push_1P1T_XKB_TS-1187A,C318884
TAS5805MPWPR,U3,TSSOP-28-1EP_4.4x9.7mm_P0.65mm_EP3.4x9.7mm_Mask3.1x4.05mm_ThermalVias,C478472

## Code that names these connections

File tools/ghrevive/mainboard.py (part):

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
YC = MAIN.centre_y
AMP_Y = YC + 0.6  # amplifier centre, pushed down to clear the bulk capacitor
LINK_PINS = ("+5V", "GND", "LED_DATA", "+3V3", "I2C_SDA", "I2C_SCL", "VMIC", "PDM_DAT", "GND", "PDM_CLK")
LINK_LABELS = ("5V", "GND", "LED", "3V3", "SDA", "SCL", "VMIC", "DAT", "GND", "CLK")
LINK_X, LINK_Y0, LINK_PITCH = 2.6, YC - 11.43, 2.54

S3_NETS = {
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    "4": "PDM_CLK_S3", "5": "PDM_DAT", "6": "LED_DATA_S3", "7": "MUTE_STATE", "8": "MUTE_SET_N",
    "9": "I2C_SDA", "10": "I2C_SCL", "13": "USB_DN", "14": "USB_DP",
    "17": "I2S_BCLK", "18": "I2S_LRCK", "19": "I2S_DOUT", "20": "I2S_REF", "21": "AMP_PDN", "22": "AMP_FAULT",
    "23": "BT_GPIO", "24": "SPARE_IO47", "25": "SPARE_IO48", "27": "S3_BOOT",
    "31": "BT_BCLK", "32": "BT_LRCK", "33": "BT_DATA", "34": "BT_TXD", "35": "BT_RXD",
    "36": "S3_RXD0", "37": "S3_TXD0", "38": "BT_EN_CTL", "39": "BT_BOOT_CTL",
}
BT_NETS = {
    "1": "GND", "15": "GND", "38": "GND", "39": "GND", "2": "+3V3", "3": "BT_EN", "25": "BT_BOOT",
    "30": "BT_BCLK", "31": "BT_LRCK", "33": "BT_DATA", "34": "BT_RXD", "35": "BT_TXD", "36": "BT_GPIO",
}
AMP_NETS = {
    "1": "GND", "5": "GND", "14": "GND", "19": "GND", "24": "GND", "29": "GND",
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

def _buck_5v() -> list[Part]:
    nets = {"1": "GND", "2": "SW_5V", "3": "PVDD", "4": "FB_5V", "6": "BOOT_5V"}  # pin 5 EN floats = enabled
    return [
        Part("U4", "TPS54302DDCR", SOT23_6, 40.9, 12.1, 180, nets=nets, lcsc="C311983", note="16.5 V -> 5.07 V, 3 A"),
        cap_10u_50v("C3", 41.0, 8.5, 180, "PVDD"),
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        cap("C24", "1uF", 60.6, AMP_Y + 6.3, 0, "AMP_AVDD"),
        # bootstrap caps follow the pin order of the right-hand row (26/25 A_P, 23/22 A_N, 21/20 B_N, 18/17 B_P):
        # column x 69.2 = A_P, B_N, B_P; column x 70.9 = A_N, reached through the 1.5 mm gap between C25 and C27.
        # The stem is only 14 mm high: the PVDD 100 nF caps lie flat above pin 28 and below pin 15, inside the edge.
        cap("C6", "100nF", 66.6, AMP_Y - 6.35, 0, "PVDD"),
        cap("C25", "470nF", 69.2, AMP_Y - 3.1, 270, "OUT_A_P", "BST_A_P"),
        cap("C27", "470nF", 69.2, AMP_Y + 0.95, 270, "BST_B_N", "OUT_B_N"),
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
